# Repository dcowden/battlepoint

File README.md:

# BattlePoint

A real-life capture the flag controller

# TODO

## Electrical
 * Shield cannot extend over UNO USB block
 * Owner and Capture LED strands reversed
 * More room 
 * more room for heat sink ( was hitting stuff around it)
 * add connx2 for switch 
 * add 2x 1000uf caps near LED strips
 * BUG: vmonitor connects to vin of regulator, not vin of arduino
 * BUG: not enough room for terminal block
 * Change terminal block footprint to conn JST XH
 * BUG: audio: chnage to JSTx05, add ground pin
 * Button board: latch has to go inwards
 * switch to microusb breakout and USB for lights, and TYPEA USB for each led strand
 * merge 620 and 330 ohm (R4 and R5) to 1x 1k instead
 * 

## Mechanical
 * More room between OLED board and Button board ( they overlap now)
 * Bigger Channels for lights. Maybe just keep the back partially open
 * more room around buttons. they tend to get tangled with wires
 * The bezel needs to cover the non-interactive part of the OLED display

## Programming
 * make # of lights on each strand configurable
 * change defaults to 20 lights on each strand
 * remove debug
 * in cp mode, we have captured the control point shouldnt play, since victory is immediate
 * in KOTH, the countdown gets behind the numbers. better to just play the countdown as one recording
 * record new sounds

 # Enhancements

 ## Easier to make and higher mast
 The led strips should be in a mast that extends upwards, making it easier to make and better visibilty too

 ## Three Player Mode
Three player mode would require another LED strip and another button. The rules are as follows:

in **KOTH** each color tracks separately. the first time to run their timer out wins
in **AD** mode  two teams are attacking and one is defending. But the winning team is the one which accumulates the most time towards the capture.
in **CP** mode the point tracks all three colors separately

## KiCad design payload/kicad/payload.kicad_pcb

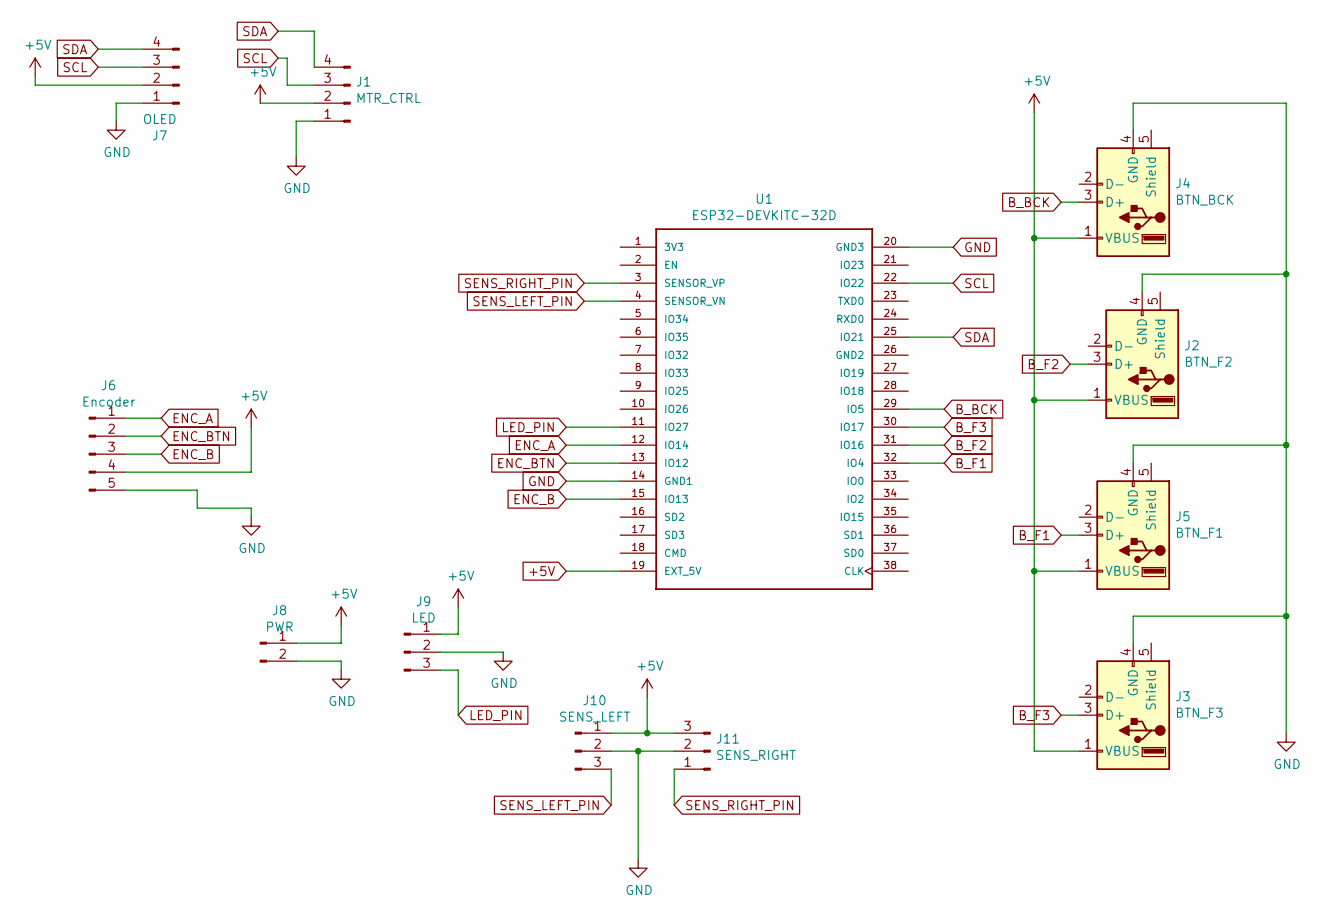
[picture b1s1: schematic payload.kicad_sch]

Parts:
J1: MTR_CTRL; JST_XH_B4B-XH-A_1x04_P2.50mm_Vertical
J2: BTN_F2; USB_A_Molex_105057_Vertical
J3: BTN_F3; USB_A_Molex_105057_Vertical
J4: BTN_BCK; USB_A_Molex_105057_Vertical
J5: BTN_F1; USB_A_Molex_105057_Vertical
J6: Encoder; JST_XH_B5B-XH-AM_1x05_P2.50mm_Vertical
J7: OLED; JST_XH_B4B-XH-AM_1x04_P2.50mm_Vertical
J8: PWR; JST_XH_B2B-XH-AM_1x02_P2.50mm_Vertical
J9: LED; JST_XH_B3B-XH-AM_1x03_P2.50mm_Vertical
J10: SENS_LEFT; JST_XH_B3B-XH-AM_1x03_P2.50mm_Vertical
J11: SENS_RIGHT; JST_XH_B3B-XH-AM_1x03_P2.50mm_Vertical
U1: ESP32-DEVKITC-32D; MODULE_ESP32-DEVKITC-32D

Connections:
+5V: J1.2, J2.1 (VBUS), J3.1 (VBUS), J4.1 (VBUS), J5.1 (VBUS), J6.4, J7.2, J8.1, J9.1, J10.1, J11.3, U1.19 (EXT_5V)
B_BCK: J4.3 (D+), U1.29 (IO5)
B_F1: J5.3 (D+), U1.32 (IO4)
B_F2: J2.3 (D+), U1.31 (IO16)
B_F3: J3.3 (D+), U1.30 (IO17)
ENC_A: J6.1, U1.12 (IO14)
ENC_B: J6.3, U1.15 (IO13)
ENC_BTN: J6.2, U1.13 (IO12)
GND: J1.1, J2.4 (GND), J3.4 (GND), J4.4 (GND), J5.4 (GND), J6.5, J7.1, J8.2, J9.2, J10.2, J11.2, U1.14 (GND1), U1.20 (GND3)
LED_PIN: J9.3, U1.11 (IO27)
SCL: J1.3, J7.3, U1.22 (IO22)
SDA: J1.4, J7.4, U1.25 (IO21)
SENS_LEFT_PIN: J10.3, U1.4 (SENSOR_VN)
SENS_RIGHT_PIN: J11.1, U1.3 (SENSOR_VP)

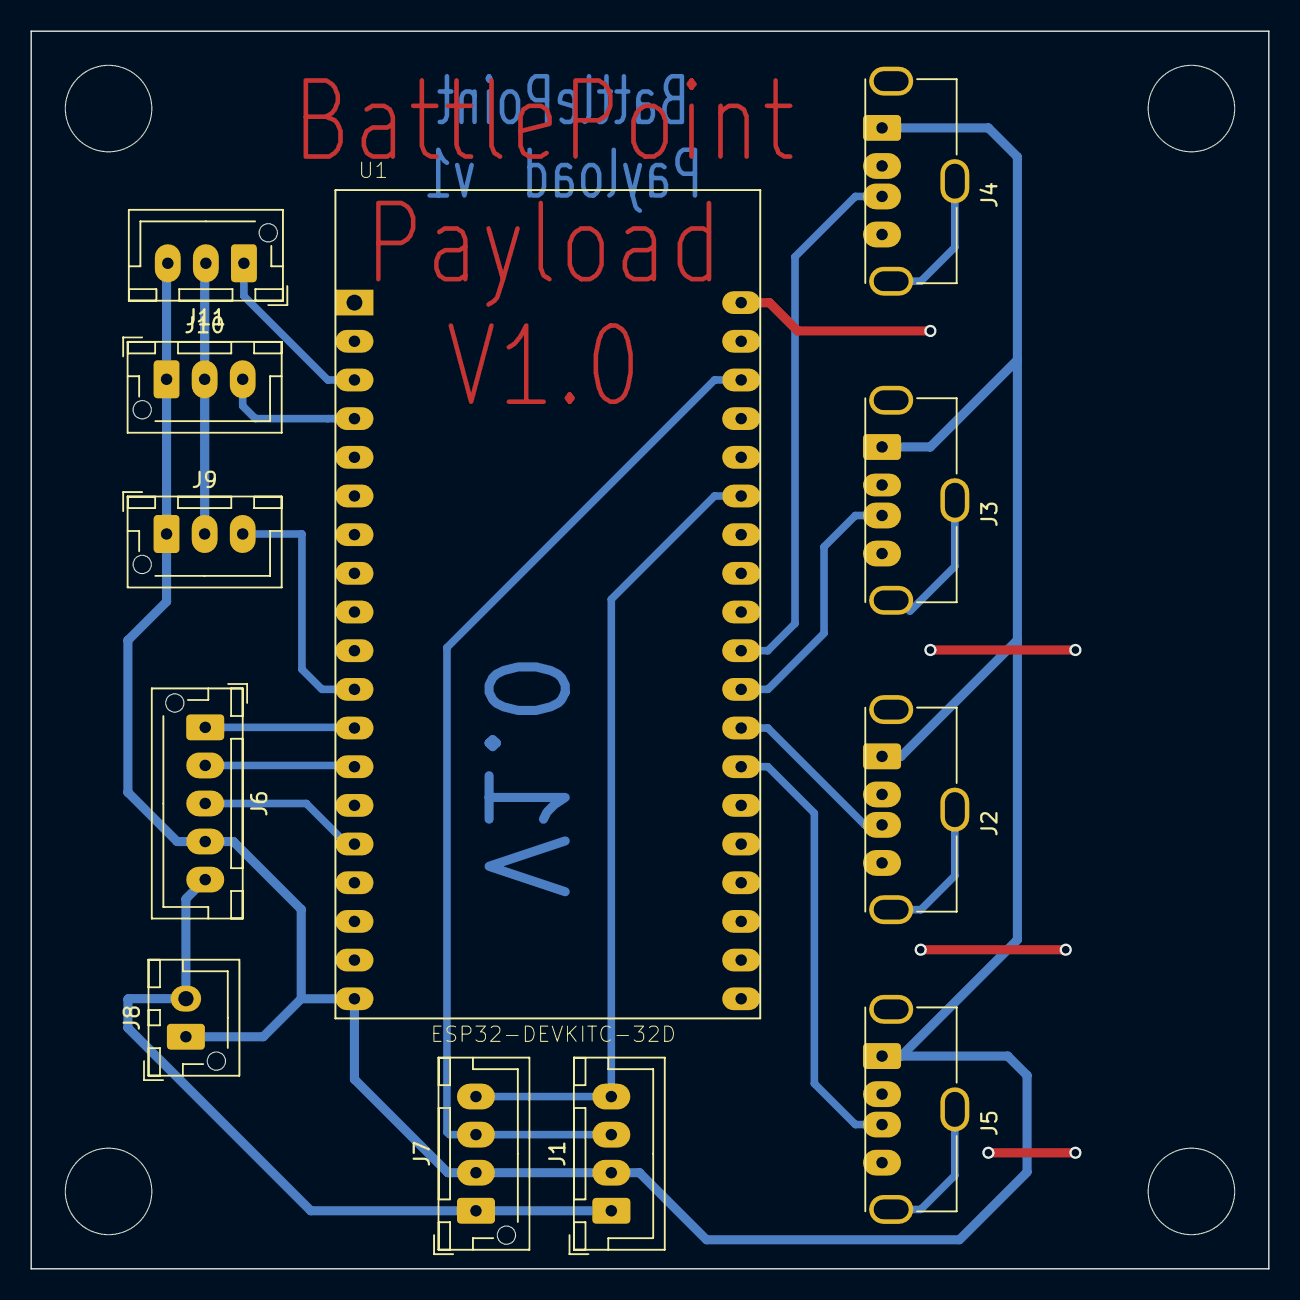
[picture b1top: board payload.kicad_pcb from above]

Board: 2 copper layers, 81.3 x 81.3 mm, 12 parts (0 on the bottom side), 14 nets.

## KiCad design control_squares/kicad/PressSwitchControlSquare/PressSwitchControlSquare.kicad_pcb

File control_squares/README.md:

# BattlePoint - Real-Life Team Fortress 2 Game

A Python/NiceGUI implementation of a real-life Team Fortress 2 style capture point game using Raspberry Pi, Bluetooth tags, and physical equipment.

## Features

- **Three Game Modes:**
  - KOTH (King of the Hill): Teams must hold point for time limit
  - AD (Attack/Defend): Blue attacks, Red defends
  - CP (Control Point): Team with most capture time wins

- **Real-time UI:**
  - Live game clock
  - Team meters (Red/Blue)
  - Seesaw balance meter
  - Control point status with progress
  - Event feed

- **Backend Features:**
  - Bluetooth tag scanning for player/equipment tracking
  - Proximity detection with configurable thresholds
  - Event management with sound triggers
  - Settings persistence
  - Comprehensive test suite

## Hardware Requirements

- Raspberry Pi (3B+ or newer recommended)
- Bluetooth Low Energy tags (advertising at 50ms rate)
- WiFi capability for hosting game network
- Optional: Speaker for sound effects
- Optional: LED strips for visual feedback

## Software Requirements

- Python 3.9 or newer
- See requirements.txt for dependencies

## Installation

### 1. Clone/Download the project

```bash
git clone <repository_url>
cd battlepoint
```

### 2. Create virtual environment

```bash
python3 -m venv venv
source venv/bin/activate  # On Windows: venv\Scripts\activate
```

### 3. Install dependencies

```bash
pip install -r requirements.txt
```

### 4. Run the application

```bash
python battlepoint_game.py
```

### 5. Access the UI

Open a browser and navigate to:
- Game UI: http://localhost:8080/game
- Settings: http://localhost:8080/settings
- Debug Console: http://localhost:8080/debug

## Configuration

### Game Settings (via Settings UI)

- **Game Mode**: KOTH, AD, or CP
- **Time Limit**: Total game duration (10-600 seconds)
- **Capture Time**: Time to capture point (5-120 seconds)
- **Button Threshold**: Proximity timeout (1-30 seconds)
- **Start Delay**: Countdown before game starts (0-60 seconds)

### Bluetooth Tag Protocol

Tags should advertise with the following binary format:

```
Byte 0: Tag Type (1=Player, 2=Control Square, 3=Health Square)
Byte 1-2: Tag ID (uint16, unique across all tags)
Byte 3: Team (1=RED, 2=BLU, 3=NOBODY)
Bytes 4+: Tag-specific data (reserved for future use)
```

### Service UUID

Set your Bluetooth service UUID in the code:
```python
scanner.service_uuid = "YOUR_SERVICE_UUID_HERE"
```

## API Endpoints

### Game Control
- `POST /api/start` - Start a new game
- `POST /api/stop` - Stop/cancel current game
- `GET /api/state` - Get current game state
- `POST /api/configure` - Update game options

### Proximity Simulation (for testing)
- `POST /api/proximity/red` - Simulate red team proximity
- `POST /api/proximity/blue` - Simulate blue team proximity

### Settings
- `POST /api/settings/save` - Save settings to disk
- `GET /api/settings/load` - Load settings from disk

### Sound (if enabled)
- `POST /api/sound/play/{sound_id}` - Play sound effect
- `POST /api/sound/volume/{volume}` - Set volume (0-30)

### Bluetooth
- `GET /api/bluetooth/tags` - Get active Bluetooth tags
- `POST /api/bluetooth/start` - Start BLE scanning
- `POST /api/bluetooth/stop` - Stop BLE scanning

## Testing

Run the test suite:

```bash
pytest test_battlepoint.py -v
```

Run with coverage:

```bash
pytest test_battlepoint.py --cov=battlepoint_game --cov-report=html
```

## Architecture

### Backend (runs independently)
- **Clock**: Time abstraction (real or test)
- **Proximity**: Tracks player positions via Bluetooth
- **ControlPoint**: Capture logic and state
- **EventManager**: Game events with cooldowns
- **Game**: Base game logic
  - KothGame: King of the Hill implementation
  - ADGame: Attack/Defend implementation
  - CPGame: Control Point implementation
- **BluetoothScanner**: BLE tag detection
- **SoundSystem**: Audio playback
- **SettingsManager**: Persistence

### Frontend (NiceGUI)
- **Game UI** (`/game`): Main game interface
- **Settings UI** (`/settings`): Configuration
- **Debug UI** (`/debug`): Testing and monitoring

### FastAPI
- REST endpoints for backend control
- WebSocket support for real-time updates
- Background task for game loop (100ms update rate)

## Customization

### Adding Sound Effects

1. Place MP3 files in a `sounds/` directory
2. Update the sound map in `SoundSystem.play()`:

```python
sound_map = {
    1: "your_sound.mp3",
    2: "another_sound.mp3",
    # ...
}
```

3. Call sounds via API or event manager

### Adding LED Support

For Raspberry Pi GPIO LEDs:

```python
# Install RPi.GPIO
pip install RPi.GPIO

# In your code:
import RPi.GPIO as GPIO

class LEDController:
    def __init__(self):
        GPIO.setmode(GPIO.BCM)
        self.red_pin = 17
        self.blue_pin = 27
        GPIO.setup(self.red_pin, GPIO.OUT)
        GPIO.setup(self.blue_pin, GPIO.OUT)
    
    def set_red(self, on: bool):
        GPIO.output(self.red_pin, GPIO.HIGH if on else GPIO.LOW)
    
    def set_blue(self, on: bool):
        GPIO.output(self.blue_pin, GPIO.HIGH if on else GPIO.LOW)
```

### Implementing Real Bluetooth Scanning

Replace the stub implementation in `BluetoothScanner`:

```python
from bleak import BleakScanner

async def start_scanning(self):
    self._scanning = True
    
    def detection_callback(device, advertisement_data):
        if self.service_uuid in advertisement_data.service_uuids:
            # Parse manufacturer data or service data
            raw_data = advertisement_data.manufacturer_data.get(0xFFFF)
            if raw_data:
                tag = self.parse_tag_data(bytes(raw_data))
                if tag:
                    self.tags[tag.id] = tag
    
    scanner = BleakScanner(detection_callback=detection_callback)
    await scanner.start()
    
    while self._scanning:
        await asyncio.sleep(0.05)  # 50ms scan rate
    
    await scanner.stop()
```

## Deployment on Raspberry Pi

### 1. Enable Bluetooth

```bash
sudo apt-get update
sudo apt-get install bluetooth bluez python3-bluez
sudo systemctl enable bluetooth
sudo systemctl start bluetooth
```

### 2. Set up WiFi Access Point

```bash
sudo apt-get install hostapd dnsmasq
# Configure hostapd.conf and dnsmasq.conf
# See: https://www.raspberrypi.org/documentation/configuration/wireless/access-point.md
```

### 3. Run as service

Create `/etc/systemd/system/battlepoint.service`:

```ini
[Unit]
Description=BattlePoint Game Server
After=network.target

[Service]
Type=simple
User=pi
WorkingDirectory=/home/pi/battlepoint
ExecStart=/home/pi/battlepoint/venv/bin/python battlepoint_game.py
Restart=on-failure

[Install]
WantedBy=multi-user.target
```

Enable and start:

```bash
sudo systemctl enable battlepoint
sudo systemctl start battlepoint
```

## Troubleshooting

### Bluetooth not working
- Ensure Bluetooth is enabled: `sudo systemctl status bluetooth`
- Check permissions: `sudo usermod -a -G bluetooth $USER`
- Test scanning: `sudo hcitool lescan`

### UI not accessible
- Check firewall: `sudo ufw allow 8080`
- Verify server is running: `sudo systemctl status battlepoint`
- Check logs: `journalctl -u battlepoint -f`

### Game not updating
- Check backend is running: Look for game loop in logs
- Verify proximity updates: Use debug UI to monitor
- Test with manual proximity buttons first

## License

[Your License Here]

## Credits

Based on the Arduino/C++ implementation by dcowden, 2017.
Python/NiceGUI port: 2024.

## Contributing

Pull requests welcome! Please ensure:
- All tests pass
- Code follows PEP 8 style
- New features include tests
- Documentation is updated

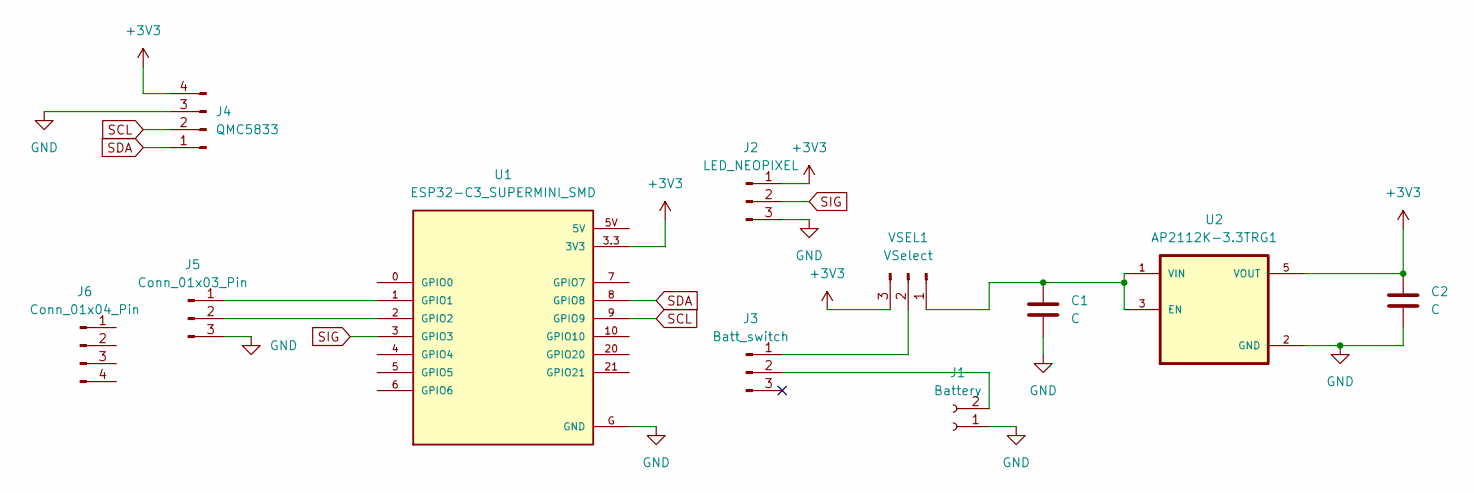
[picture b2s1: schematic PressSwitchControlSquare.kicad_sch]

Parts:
C1, C2: C; C_0603_1608Metric
J1: Battery; JST_PH_B2B-PH-SM4-TB_1x02-1MP_P2.00mm_Vertical
J2: LED_NEOPIXEL; PinHeader_1x03_P2.54mm_Vertical
J3: Batt_switch; PinHeader_1x03_P2.54mm_Vertical
J4: QMC5833; PinHeader_1x04_P2.54mm_Vertical
J5: Conn_01x03_Pin; JST_PH_B3B-PH-SM4-TB_1x03-1MP_P2.00mm_Vertical
J6: Conn_01x04_Pin
U1: ESP32-C3_SUPERMINI_SMD; MODULE_ESP32-C3_SUPERMINI
U2: AP2112K-3.3TRG1; SOT95P285X140-5N; PARTREV 2-2
VSEL1: VSelect; PinHeader_1x03_P2.54mm_Vertical

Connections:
+3V3: C2.1, J2.1, J4.4, U1.3.3 (3V3), U2.5 (VOUT), VSEL1.3
GND: C1.2, C2.2, J1.1, J2.3, J4.3, J5.3, U1.G (GND), U2.2 (GND)
unnamed: J1.2, J3.2
unnamed: J3.1, VSEL1.2
unnamed: J5.1, U1.1 (GPIO1)
unnamed: J5.2, U1.2 (GPIO2)
unnamed: C1.1, U2.1 (VIN), U2.3 (EN), VSEL1.1
SCL: J4.2, U1.9 (GPIO9)
SDA: J4.1, U1.8 (GPIO8)
SIG: J2.2, U1.3 (GPIO3)

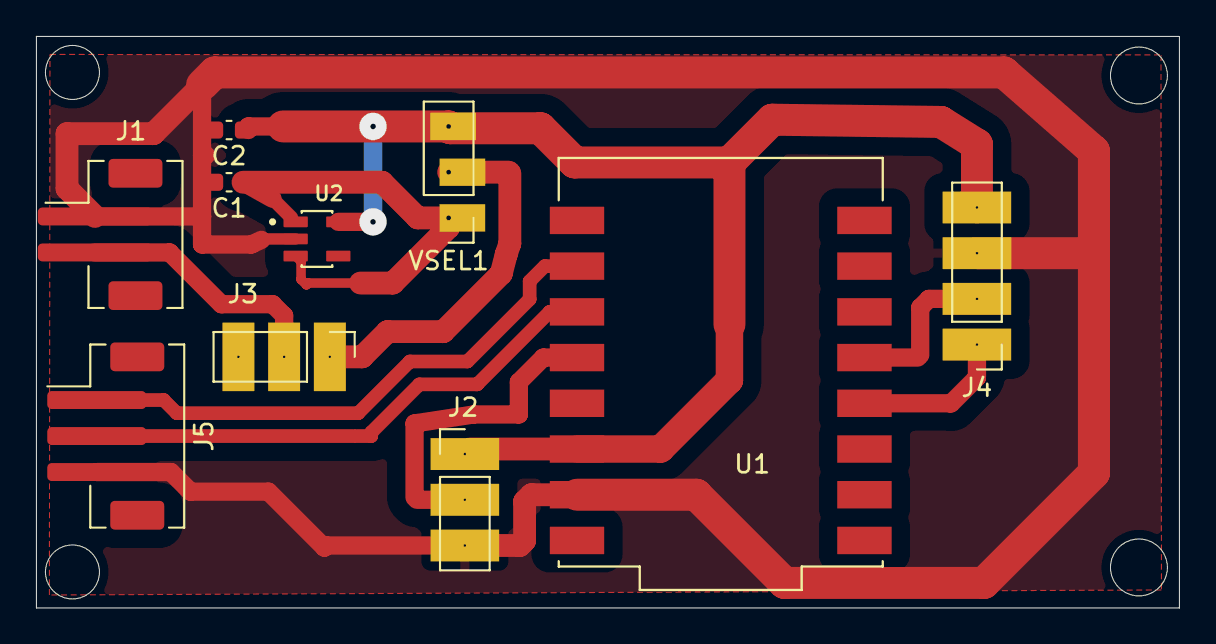
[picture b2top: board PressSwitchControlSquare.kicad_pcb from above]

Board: 2 copper layers, 63.5 x 31.8 mm, 10 parts (0 on the bottom side), 10 nets.

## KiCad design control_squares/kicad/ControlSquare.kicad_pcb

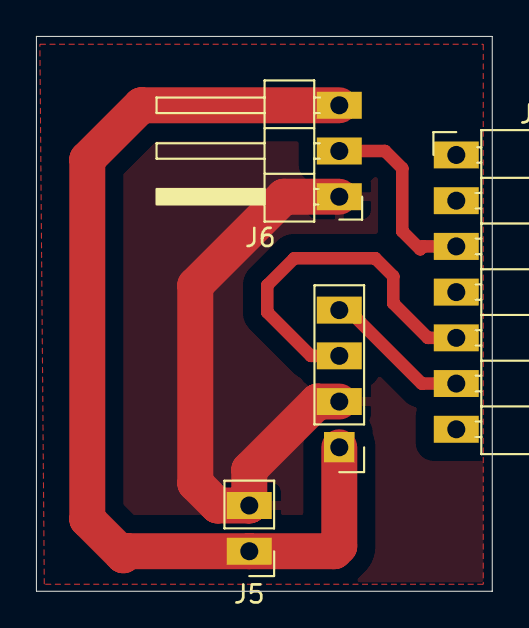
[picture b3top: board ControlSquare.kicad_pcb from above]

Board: 2 copper layers, 25.3 x 30.8 mm, 4 parts (0 on the bottom side), 5 nets.

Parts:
J1: Seed Left; PinHeader_1x07_P2.54mm_Horizontal
J3: QMC5388; PinHeader_1x04_P2.54mm_Vertical
J5: Conn_01x02_Pin; PinHeader_1x02_P2.54mm_Vertical
J6: LED; PinHeader_1x03_P2.54mm_Horizontal

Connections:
+3.3V: J3.1, J5.1, J6.3
GND: J3.2, J5.2, J6.1
LED: J1.3, J6.2
SCL: J1.5, J3.3
SDA: J1.6, J3.4

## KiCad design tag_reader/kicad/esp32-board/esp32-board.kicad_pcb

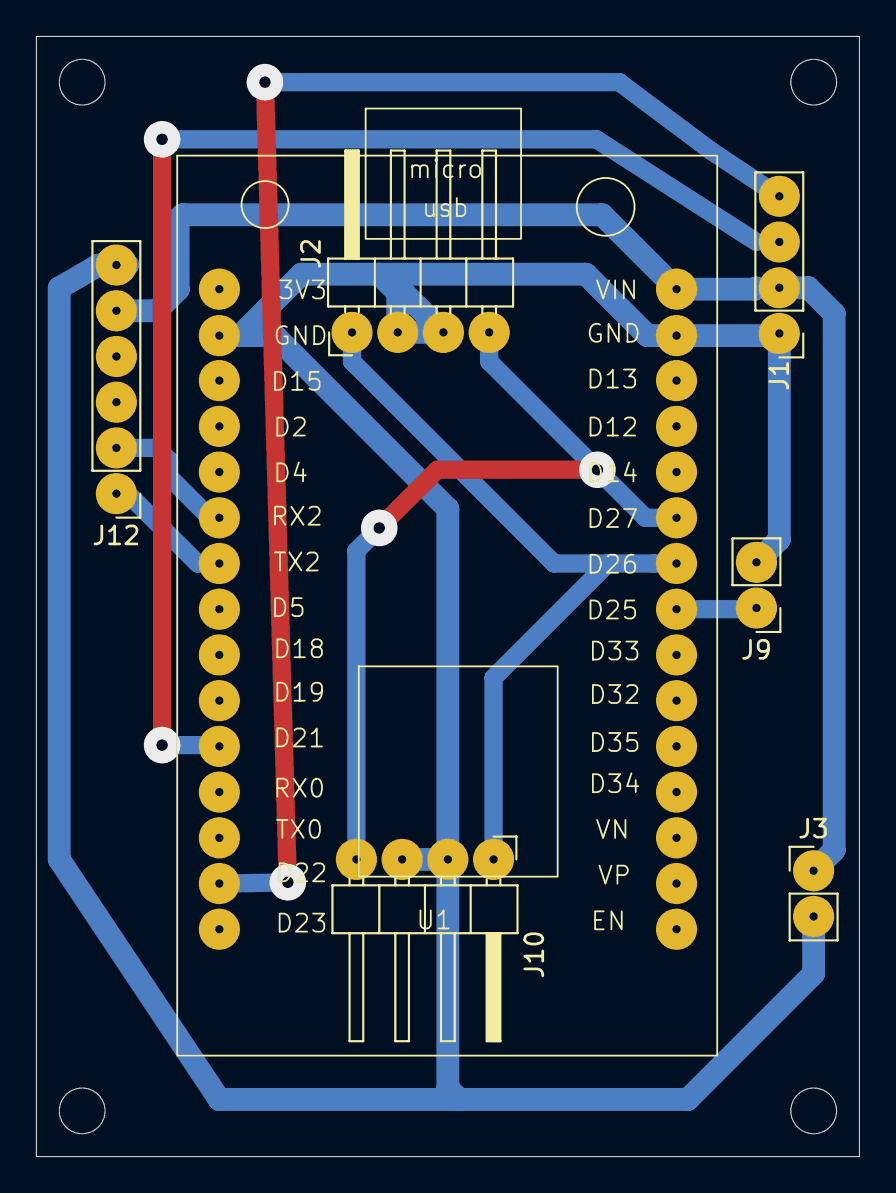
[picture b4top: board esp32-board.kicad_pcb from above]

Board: 2 copper layers, 45.7 x 62.2 mm, 7 parts (0 on the bottom side), 11 nets.

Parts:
J1: OLED; PinHeader_1x04_P2.54mm_Vertical
J2: SW_RIGHT; PinHeader_1x04_P2.54mm_Horizontal
J3: PWR; PinHeader_1x02_P2.54mm_Vertical
J9: SPK; PinHeader_1x02_P2.54mm_Vertical
J10: SW_LEFT; PinHeader_1x04_P2.54mm_Horizontal
J12: LID; PinHeader_1x06_P2.54mm_Vertical
U1: ESP32-DEVKITV1

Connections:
D26: J2.1, J10.1, U1.24 (D26)
D27: J2.4, J10.4, U1.25 (D27)
GND: J1.1, J2.2, J2.3, J3.2, J9.2, J10.2, J10.3, J12.6, U1.2 (GND), U1.29 (GND)
LED1: J12.3, U1.26 (D14)
LED2: J12.4, U1.27 (D12)
RX2: J12.2, U1.6 (RX2)
SCL: J1.3, U1.11 (D21/SCL)
SDA: J1.4, U1.14 (D22)
SPK: J9.1, U1.23 (D25)
TX2: J12.1, U1.7 (TX2)
VCC: J1.2, J3.1, J12.5, U1.30 (VIN)

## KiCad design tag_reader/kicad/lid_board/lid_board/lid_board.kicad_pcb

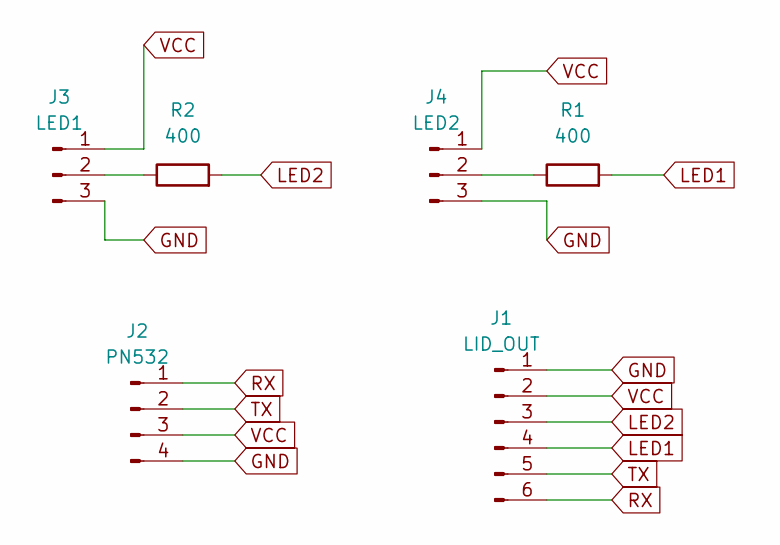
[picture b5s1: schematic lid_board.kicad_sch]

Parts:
J1: LID_OUT; PinHeader_1x06_P2.54mm_Horizontal
J2: PN532; PinHeader_1x04_P2.54mm_Vertical
J3: LED1; PinHeader_1x03_P2.54mm_Vertical
J4: LED2; PinHeader_1x03_P2.54mm_Vertical
R1, R2: 400; R_Axial_DIN0204_L3.6mm_D1.6mm_P7.62mm_Horizontal

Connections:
GND: J1.1, J2.4, J3.3, J4.3
LED1: J1.4, R1.2
LED2: J1.3, R2.2
unnamed: J3.2, R2.1
unnamed: J4.2, R1.1
RX: J1.6, J2.1
TX: J1.5, J2.2
VCC: J1.2, J2.3, J3.1, J4.1

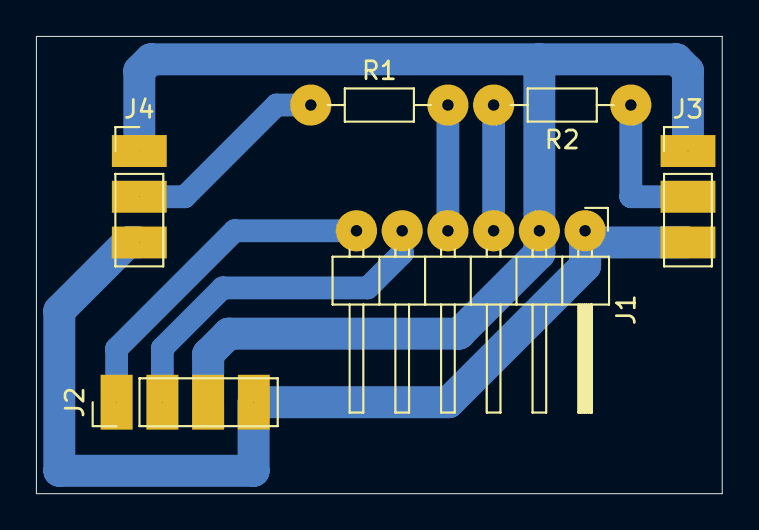
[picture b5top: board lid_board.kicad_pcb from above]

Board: 2 copper layers, 38.1 x 25.4 mm, 6 parts (0 on the bottom side), 8 nets.

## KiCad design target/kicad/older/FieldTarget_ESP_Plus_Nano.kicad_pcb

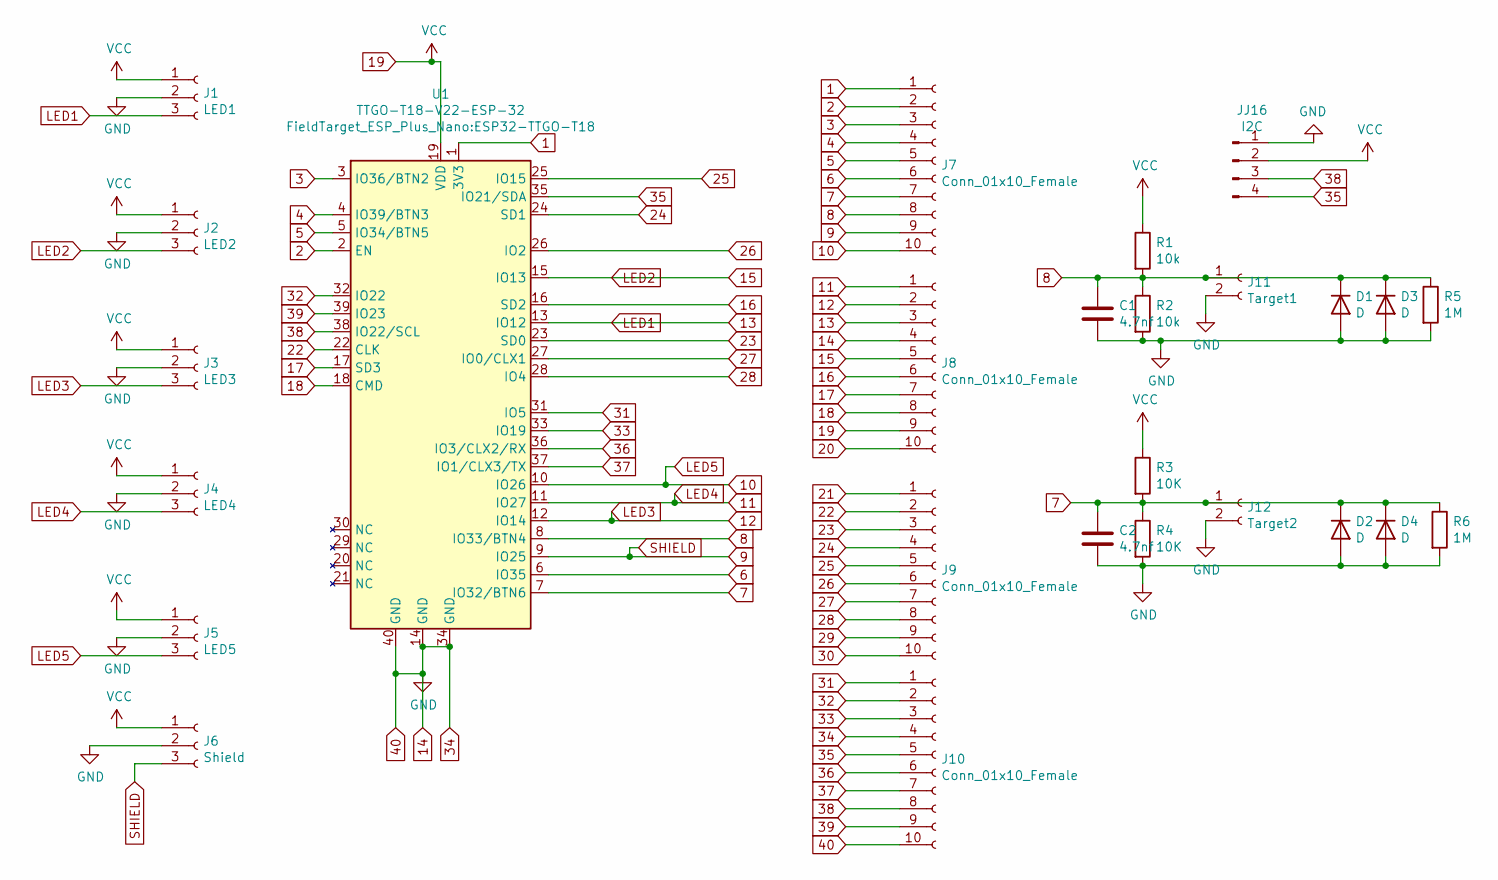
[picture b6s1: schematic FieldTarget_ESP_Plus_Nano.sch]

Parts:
C1, C2: 4.7nf; CP_Radial_D5.0mm_P2.50mm
D1: D; D_DO-34_SOD68_P7.62mm_Horizontal
D2, D3, D4: D; D_DO-35_SOD27_P7.62mm_Horizontal
J1: LED1; PinSocket_1x03_P2.54mm_Vertical
J2: LED2; PinSocket_1x03_P2.54mm_Vertical
J3: LED3; PinSocket_1x03_P2.54mm_Vertical
J4: LED4; PinSocket_1x03_P2.54mm_Vertical
J5: LED5; PinSocket_1x03_P2.54mm_Vertical
J6: Shield; PinHeader_1x03_P2.54mm_Vertical
J7, J8, J9, J10: Conn_01x10_Female; PinHeader_1x10_P2.54mm_Vertical
J11: Target1; JST_XH_B2B-XH-AM_1x02_P2.50mm_Vertical
J12: Target2; JST_XH_B2B-XH-AM_1x02_P2.50mm_Vertical
JJ16: I2C; JST_XH_B4B-XH-AM_1x04_P2.50mm_Vertical
R1, R2: 10k; R_Axial_DIN0207_L6.3mm_D2.5mm_P10.16mm_Horizontal
R3, R4: 10K; R_Axial_DIN0207_L6.3mm_D2.5mm_P10.16mm_Horizontal
R5, R6: 1M; R_Axial_DIN0207_L6.3mm_D2.5mm_P10.16mm_Horizontal
U1: TTGO-T18-V22-ESP-32; ESP32-TTGO-T18

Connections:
1: J7.1, U1.1 (3V3)
2: J7.2, U1.2 (EN)
3: J7.3, U1.3 (IO36/BTN2)
4: J7.4, U1.4 (IO39/BTN3)
5: J7.5, U1.5 (IO34/BTN5)
6: J7.6, U1.6 (IO35)
7: C2.1, D2.1 (K), D4.1 (K), J7.7, J12.1, R3.2, R4.1, R6.1, U1.7 (IO32/BTN6)
8: C1.1, D1.1 (K), D3.1 (K), J7.8, J11.1, R1.2, R2.1, R5.1, U1.8 (IO33/BTN4)
9: J6.3, J7.9, U1.9 (IO25)
10: J5.3, J7.10, U1.10 (IO26)
11: J4.3, J8.1, U1.11 (IO27)
12: J3.3, J8.2, U1.12 (IO14)
13: J1.3, J8.3, U1.13 (IO12)
14: C1.2, C2.2, D1.2 (A), D2.2 (A), D3.2 (A), D4.2 (A), J1.2, J2.2, J3.2, J4.2, J5.2, J6.2, J8.4, J10.4, J10.10, J11.2, J12.2, JJ16.1, R2.2, R4.2, R5.2, R6.2, U1.14 (GND), U1.34 (GND), U1.40 (GND)
15: J2.3, J8.5, U1.15 (IO13)
16: J8.6, U1.16 (SD2)
17: J8.7, U1.17 (SD3)
18: J8.8, U1.18 (CMD)
19: J1.1, J2.1, J3.1, J4.1, J5.1, J6.1, J8.9, JJ16.2, R1.1, R3.1, U1.19 (VDD)
20: J8.10
21: J9.1
22: J9.2, U1.22 (CLK)
23: J9.3, U1.23 (SD0)
24: J9.4, U1.24 (SD1)
25: J9.5, U1.25 (IO15)
26: J9.6, U1.26 (IO2)
27: J9.7, U1.27 (IO0/CLX1)
28: J9.8, U1.28 (IO4)
29: J9.9
30: J9.10
31: J10.1, U1.31 (IO5)
32: J10.2, U1.32 (IO22)
33: J10.3, U1.33 (IO19)
35: J10.5, JJ16.4, U1.35 (IO21/SDA)
36: J10.6, U1.36 (IO3/CLX2/RX)
37: J10.7, U1.37 (IO1/CLX3/TX)
38: J10.8, JJ16.3, U1.38 (IO22/SCL)
39: J10.9, U1.39 (IO23)

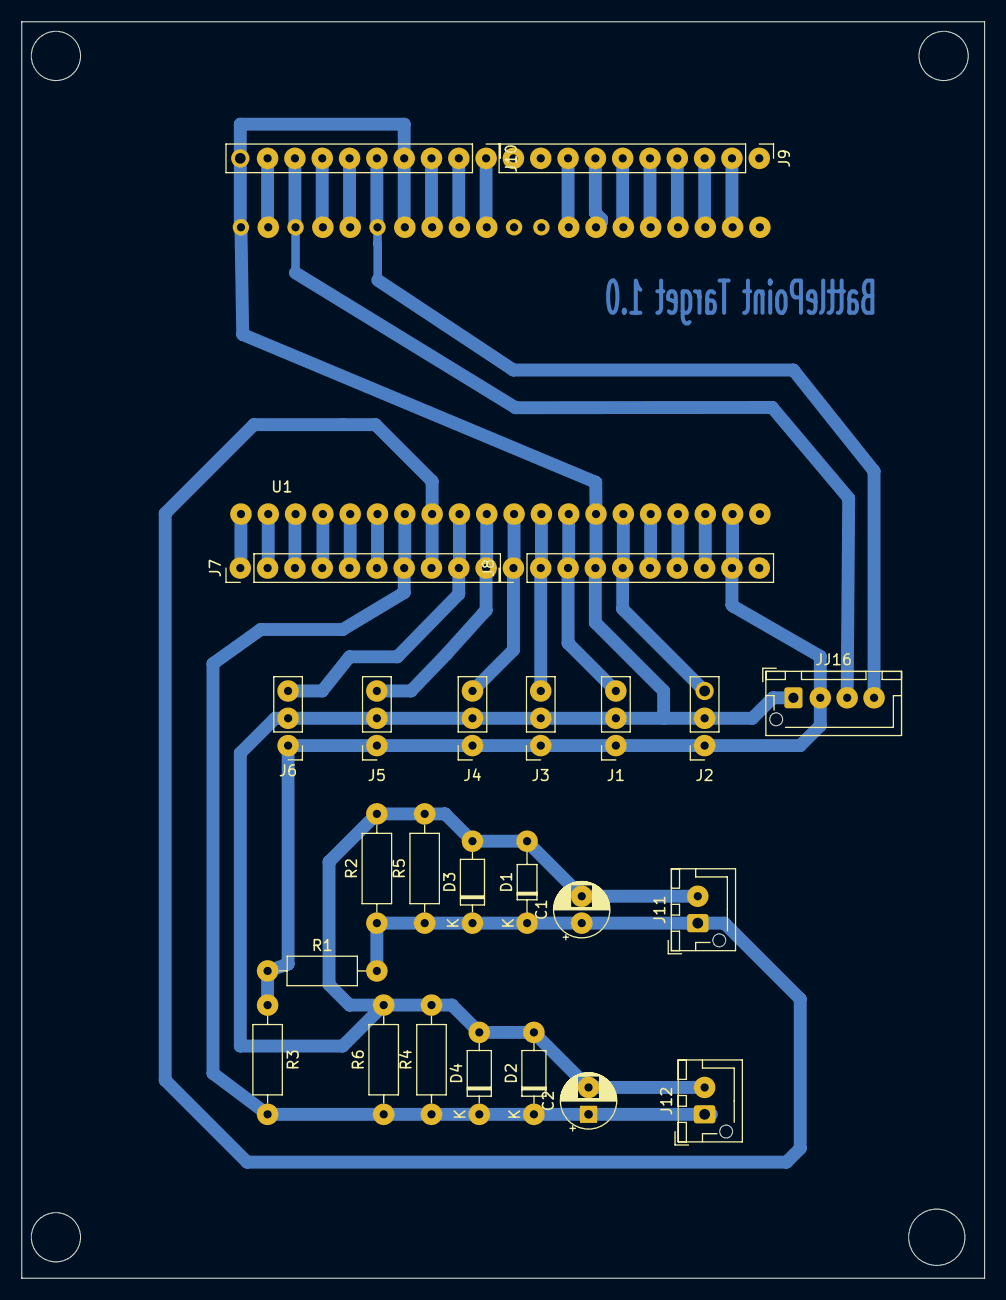
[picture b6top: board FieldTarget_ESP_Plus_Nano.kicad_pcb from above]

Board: 2 copper layers, 89.5 x 116.8 mm, 26 parts (0 on the bottom side), 34 nets.

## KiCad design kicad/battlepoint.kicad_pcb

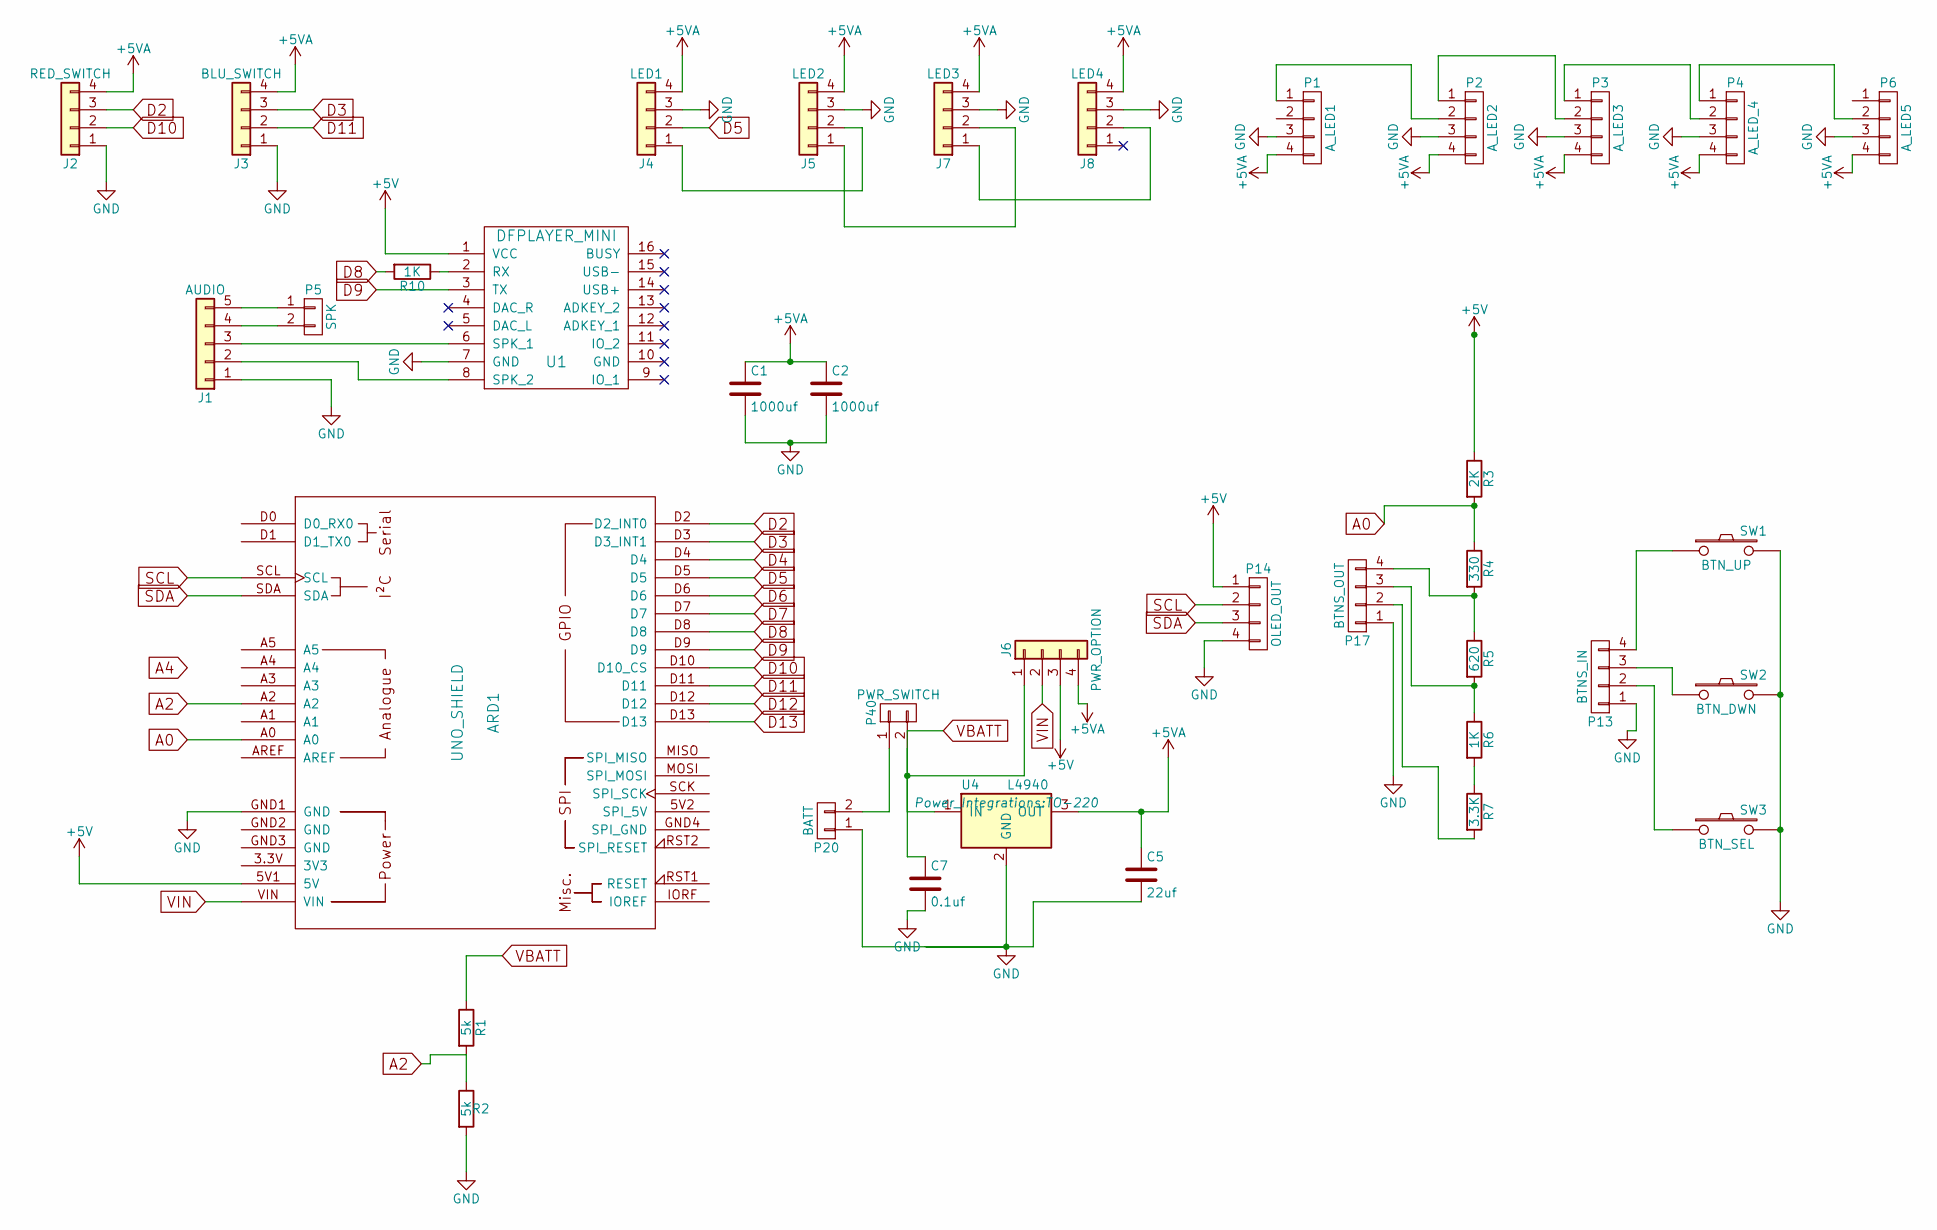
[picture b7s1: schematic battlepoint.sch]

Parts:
ARD1: UNO_SHIELD; Arduino_Uno_Shield
C1, C2: 1000uf; CP_Radial_D7.5mm_P2.50mm
C5: 22uf; C_Radial_D7.5_L11.2_P2.5
C7: 0.1uf; C_Rect_L4_W2.5_P2.5
J1: AUDIO; JST_XH_B05B-XH-A_05x2.50mm_Straight
J2: RED_SWITCH; JST_XH_B04B-XH-A_04x2.50mm_Straight
J3: BLU_SWITCH; JST_XH_B04B-XH-A_04x2.50mm_Straight
J4: LED1; JST_XH_B04B-XH-A_04x2.50mm_Straight
J5: LED2; JST_XH_B04B-XH-A_04x2.50mm_Straight
J6: PWR_OPTION; Pin_Header_Straight_1x04_Pitch2.54mm
J7: LED3; JST_XH_B04B-XH-A_04x2.50mm_Straight
J8: LED4; JST_XH_B04B-XH-A_04x2.50mm_Straight
P1: A_LED1; JST_XH_B04B-XH-A_04x2.50mm_Straight
P2: A_LED2; JST_XH_B04B-XH-A_04x2.50mm_Straight
P3: A_LED3; JST_XH_B04B-XH-A_04x2.50mm_Straight
P4: A_LED_4; JST_XH_B04B-XH-A_04x2.50mm_Straight
P5: SPK; JST_XH_B02B-XH-A_02x2.50mm_Straight
P6: A_LED5; JST_XH_B04B-XH-A_04x2.50mm_Straight
P13: BTNS_IN; Pin_Header_Straight_1x04
P14: OLED_OUT; JST_XH_B04B-XH-A_04x2.50mm_Straight
P17: BTNS_OUT; JST_XH_B04B-XH-A_04x2.50mm_Straight
P20: BATT; JST_XH_B02B-XH-A_02x2.50mm_Straight
P40: PWR_SWITCH; JST_XH_B02B-XH-A_02x2.50mm_Straight
R1, R2: 5k; Resistor_Horizontal_RM7mm
R3: 2K; Resistor_Vertical_RM5mm
R4: 330; Resistor_Vertical_RM5mm
R5: 620; Resistor_Vertical_RM5mm
R6: 1K; Resistor_Vertical_RM5mm
R7: 3.3K; Resistor_Vertical_RM5mm
R10: 1K; Resistor_Horizontal_RM7mm
SW1: BTN_UP; SW_PUSH_6mm
SW2: BTN_DWN; SW_PUSH_6mm
SW3: BTN_SEL; SW_PUSH_6mm
U1: DFPLAYER_MINI; dfplayer_mini
U4: L4940; TO-220

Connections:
+5V: ARD1.5V1 (5V), J6.3, P14.1, R3.1, U1.1 (VCC)
+5VA: C1.1, C2.1, C5.1, J2.4, J3.4, J4.4, J5.4, J6.4, J7.4, J8.4, P1.4, P2.4, P3.4, P4.4, P6.4, U4.3 (OUT)
A0: ARD1.A0, R3.2, R4.1
A2: ARD1.A2, R1.2, R2.1
D2: ARD1.D2 (D2_INT0), J2.3
D3: ARD1.D3 (D3_INT1), J3.3
D4: ARD1.D4
D5: ARD1.D5, J4.2
D6: ARD1.D6
D7: ARD1.D7
D8: ARD1.D8, R10.2
D9: ARD1.D9, U1.3 (TX)
D10: ARD1.D10 (D10_CS), J2.2
D11: ARD1.D11, J3.2
D12: ARD1.D12
D13: ARD1.D13
GND: ARD1.GND1 (GND), C1.2, C2.2, C5.2, C7.2, J1.1, J2.1, J3.1, J4.3, J5.3, J7.3, J8.3, P1.3, P2.3, P3.3, P4.3, P6.3, P13.1, P14.4, P17.1, P20.1, R2.2, SW1.2, SW2.2, SW3.2, U1.7 (GND), U4.2 (GND)
unnamed: J1.2, U1.8 (SPK_2)
unnamed: J1.3, U1.6 (SPK_1)
unnamed: J1.4, P5.2
unnamed: J1.5, P5.1
unnamed: J4.1, J5.2
unnamed: J5.1, J7.2
unnamed: J7.1, J8.2
unnamed: P1.1, P2.2
unnamed: P2.1, P3.2
unnamed: P3.1, P4.2
unnamed: P4.1, P6.2
unnamed: P13.2, SW3.1
unnamed: P13.3, SW2.1
unnamed: P13.4, SW1.1
unnamed: P17.2, R7.2
unnamed: P17.3, R5.2, R6.1
unnamed: P17.4, R4.2, R5.1
unnamed: P20.2, P40.1
unnamed: R6.2, R7.1
unnamed: R10.1, U1.2 (RX)
SCL: ARD1.SCL, P14.2
SDA: ARD1.SDA, P14.3
VBATT: C7.1, J6.1, P40.2, R1.1, U4.1 (IN)
VIN: ARD1.VIN, J6.2

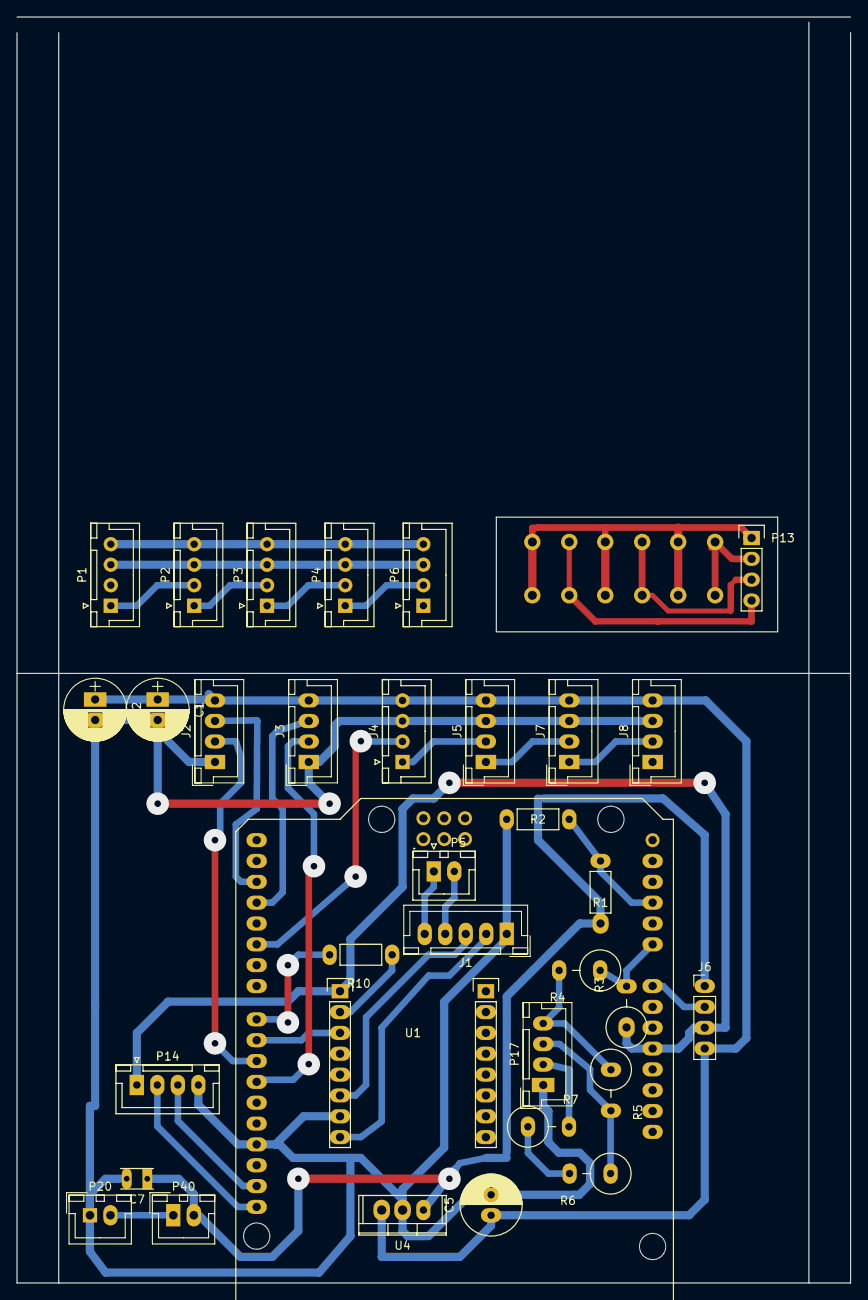
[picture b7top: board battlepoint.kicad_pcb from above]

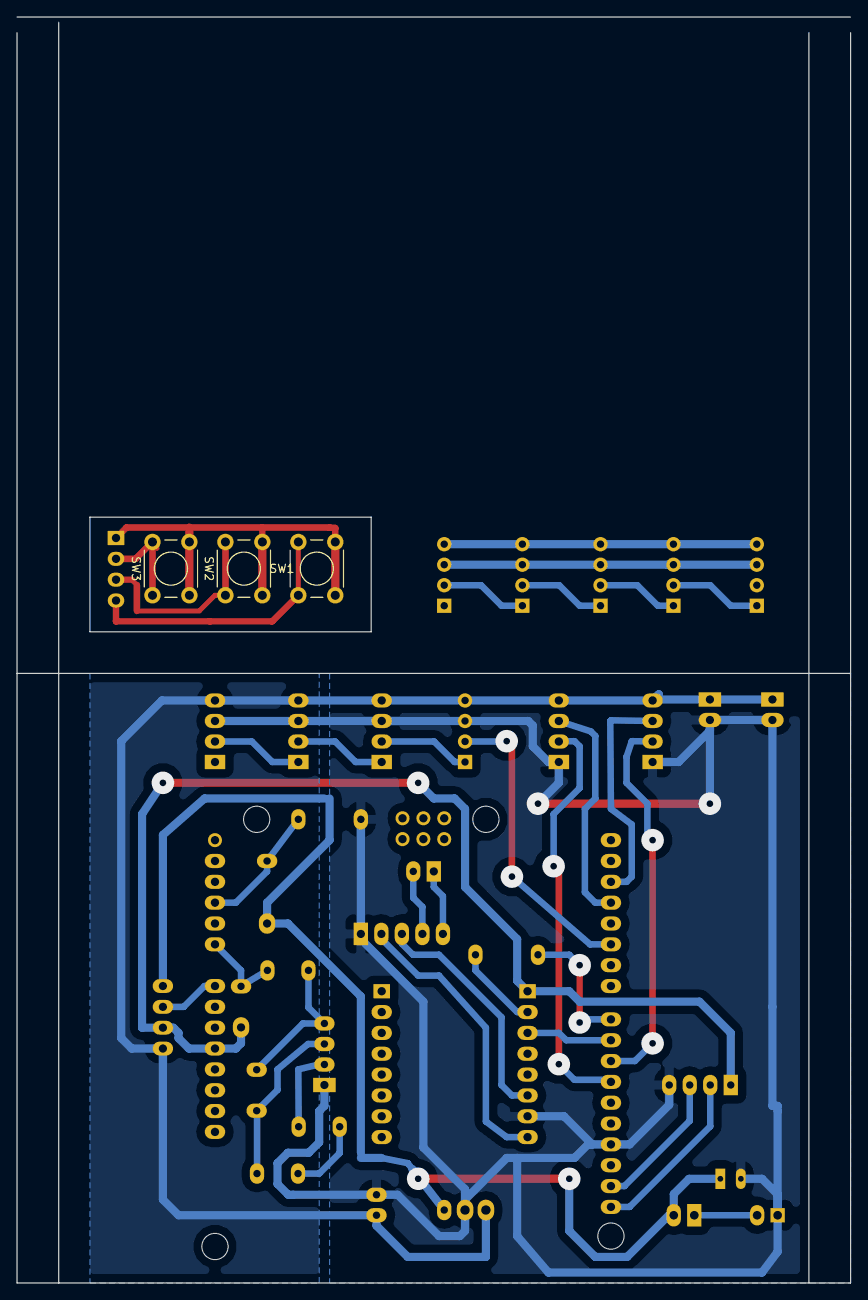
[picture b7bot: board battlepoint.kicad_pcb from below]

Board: 2 copper layers, 101.6 x 154.3 mm, 37 parts (3 on the bottom side), 36 nets.
